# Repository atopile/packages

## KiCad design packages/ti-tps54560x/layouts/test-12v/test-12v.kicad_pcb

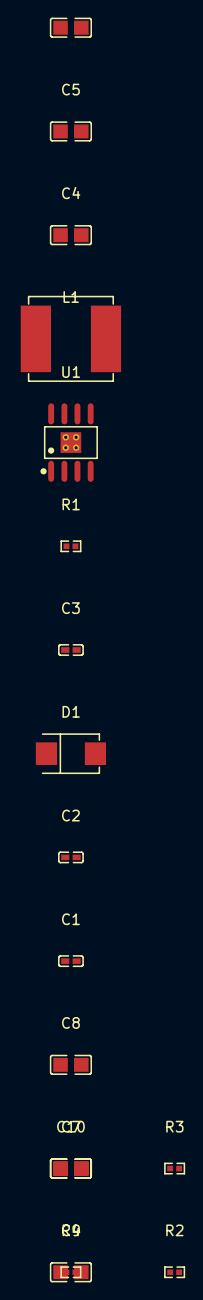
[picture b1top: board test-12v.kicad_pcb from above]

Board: 2 copper layers, 17 parts (0 on the bottom side), 9 nets, no tracks yet.

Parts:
C1: 100nF ±10% 50V X7R; C0402
C2: 4.7nF ±5% 50V C0G; C0402
C3: 8.2pF ±5% 50V C0G; C0402
C4, C5, C6: 10µF ±10% 50V X5R; C0805
C7, C8, C9, C10: 22µF ±20% 25V X5R; C0805
D1: SMB_L4.6-W3.6-LS5.3-RD
L1: IND-SMD_L8.0-W8.0_SWPA8040S
R1: 23.7kΩ ±1% 62.5mW; R0402
R2: 73.2kΩ ±1% 62.5mW; R0402
R3: 1MΩ ±1% 62.5mW; R0402
R4: 162kΩ ±1% 62.5mW; R0402
U1: SOIC-8_L5.0-W4.0-P1.27-LS6.0-BL-EP2.0

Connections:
-hv: C4.1, C5.1, C6.1, U1.2, U1.3
BOOT: C1.1, U1.1
COMP: C3.1, R1.1, U1.6
FB: R2.1, R3.2, U1.5
RT_CLK: R4.1, U1.4
cathode: C1.2, D1.1, L1.1, U1.8
gnd: C2.2, C3.2, C4.2, C5.2, C6.2, C7.2, C8.2, C9.2, C10.2, D1.2, R2.2, R4.2, U1.7, U1.9
regulator-hv: C7.1, C8.1, C9.1, C10.1, L1.2, R3.1
regulator-net: C2.1, R1.2

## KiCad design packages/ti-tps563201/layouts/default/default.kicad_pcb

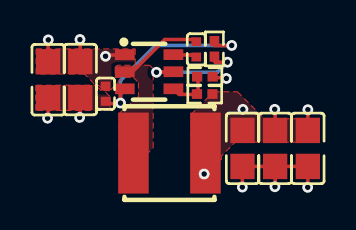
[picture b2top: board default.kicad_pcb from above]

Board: 2 copper layers, 12 parts (0 on the bottom side), 7 nets.

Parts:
C1, C4: 100nF ±10%; C0402
C2, C3, C5, C6, C7: 10µF ±10%; C0805
L1: L 2.2µH ±20%; IND-SMD_L5.0-W5.0_FNR5012S
R1: 10kΩ ±1%; R0402
R2: 20kΩ ±1%; R0402
R3: 25.5kΩ ±1%; R0402
U1: SOT-23-6_L2.9-W1.6-P0.95-LS2.8-BR

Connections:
EN: R1.1, U1.5
hv: C1.1, U1.6
input_caps[2]-power-hv: C2.1, C3.1, C4.1, R1.2, U1.3
lv: C1.2, L1.1, U1.2
output_caps[2]-power-hv: C5.1, C6.1, C7.1, L1.2, R2.1
output_caps[2]-power-lv: C2.2, C3.2, C4.2, C5.2, C6.2, C7.2, R3.2, U1.1
ref_out-hv: R2.2, R3.1, U1.4

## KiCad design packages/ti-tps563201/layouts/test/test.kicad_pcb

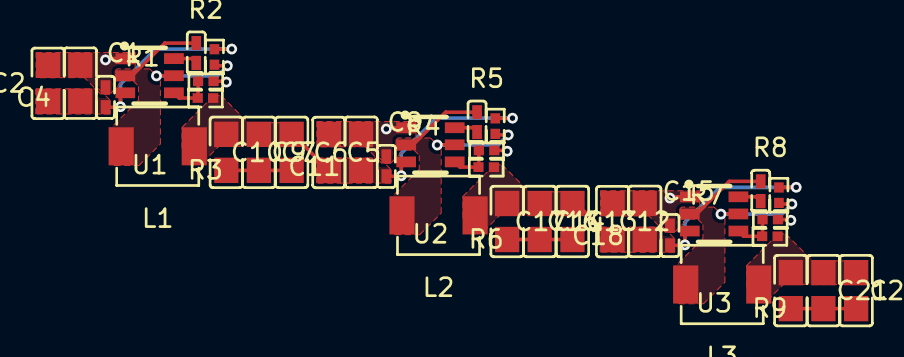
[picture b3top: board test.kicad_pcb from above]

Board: 2 copper layers, 36 parts (0 on the bottom side), 17 nets.

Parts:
C1, C4, C8, C11, C15, C18: 100nF ±10% 16V X7R; C0402
C2, C3, C5, C6, C7, C9, C10, C12, C13, C14, C16, C17, C19, C20, C21: 10µF ±10% 25V X5R; C0805
L1, L2, L3: IND-SMD_L4.4-W4.2
R1, R3, R4, R6, R7, R9: 10kΩ ±1% 62.5mW; R0402
R2: 1.5kΩ ±1% 62.5mW; R0402
R5: 1.8kΩ ±1% 62.5mW; R0402
R8: 2.49kΩ ±1% 62.5mW; R0402
U1, U2, U3: SOT-23-6_L2.9-W1.6-P0.95-LS2.8-BR

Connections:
-VIN-0: C2.1, C3.1, C4.1, R1.2, U1.3
-VIN-1: C5.1, C6.1, C7.1, C9.1, C10.1, C11.1, L1.2, R3.1, R4.2, U2.3
-VIN-2: C12.1, C13.1, C14.1, C16.1, C17.1, C18.1, L2.2, R6.1, R7.2, U3.3
gnd: C2.2, C3.2, C4.2, C5.2, C6.2, C7.2, C9.2, C10.2, C11.2, C12.2, C13.2, C14.2, C16.2, C17.2, C18.2, C19.2, C20.2, C21.2, R2.2, R5.2, R8.2, U1.1, U2.1, U3.1
hv: C19.1, C20.1, C21.1, L3.2, R9.1
regs[0]-EN: R1.1, U1.5
regs[0]-SW: C1.2, L1.1, U1.2
regs[0]-VBST: C1.1, U1.6
regs[0]-VFB: R2.1, R3.2, U1.4
regs[1]-EN: R4.1, U2.5
regs[1]-SW: C8.2, L2.1, U2.2
regs[1]-VBST: C8.1, U2.6
regs[1]-VFB: R5.1, R6.2, U2.4
regs[2]-EN: R7.1, U3.5
regs[2]-SW: C15.2, L3.1, U3.2
regs[2]-VBST: C15.1, U3.6
regs[2]-VFB: R8.1, R9.2, U3.4
